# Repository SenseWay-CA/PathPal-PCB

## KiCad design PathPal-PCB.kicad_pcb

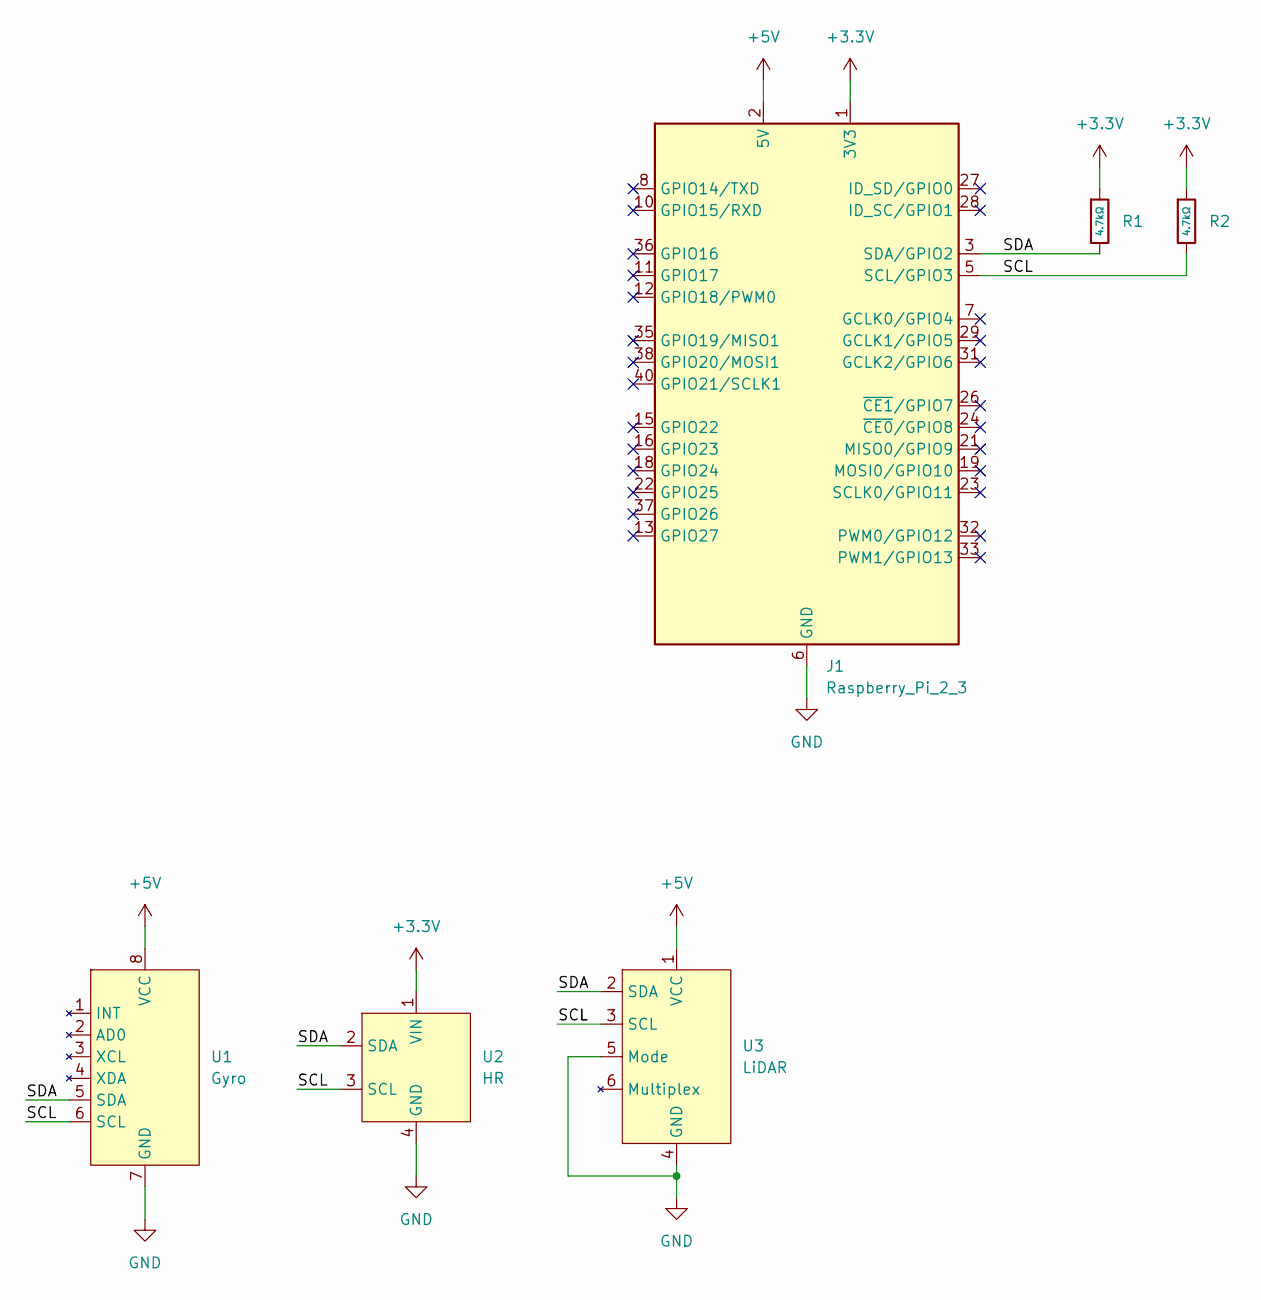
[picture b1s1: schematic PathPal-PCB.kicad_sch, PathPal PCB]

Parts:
J1: Raspberry_Pi_2_3; PinSocket_2x20_P2.54mm_Vertical
R1, R2: 4.7kΩ; R_Axial_DIN0207_L6.3mm_D2.5mm_P7.62mm_Horizontal; Overload Voltage (Max) 150V; Tolerance ±1%; Part 0805W8F4701T5E; LCSC C17673
U1: Gyro; PinSocket_1x08_P2.54mm_Vertical
U2: HR; PinSocket_1x04_P2.54mm_Vertical
U3: LiDAR; PinSocket_1x06_P2.54mm_Vertical

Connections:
+3.3V: J1.1 (3V3), J1.17 (3V3), R1.1, R2.1, U2.1 (VIN)
+5V: J1.2 (5V), J1.4 (5V), U1.8 (VCC), U3.1 (VCC)
/SCL: J1.5 (SCL/GPIO3), R2.2, U1.6 (SCL), U2.3 (SCL), U3.3 (SCL)
/SDA: J1.3 (SDA/GPIO2), R1.2, U1.5 (SDA), U2.2 (SDA), U3.2 (SDA)
GND: J1.6 (GND), J1.9 (GND), J1.14 (GND), J1.20 (GND), J1.25 (GND), J1.30 (GND), J1.34 (GND), J1.39 (GND), U1.7 (GND), U2.4 (GND), U3.4 (GND), U3.5 (Mode)

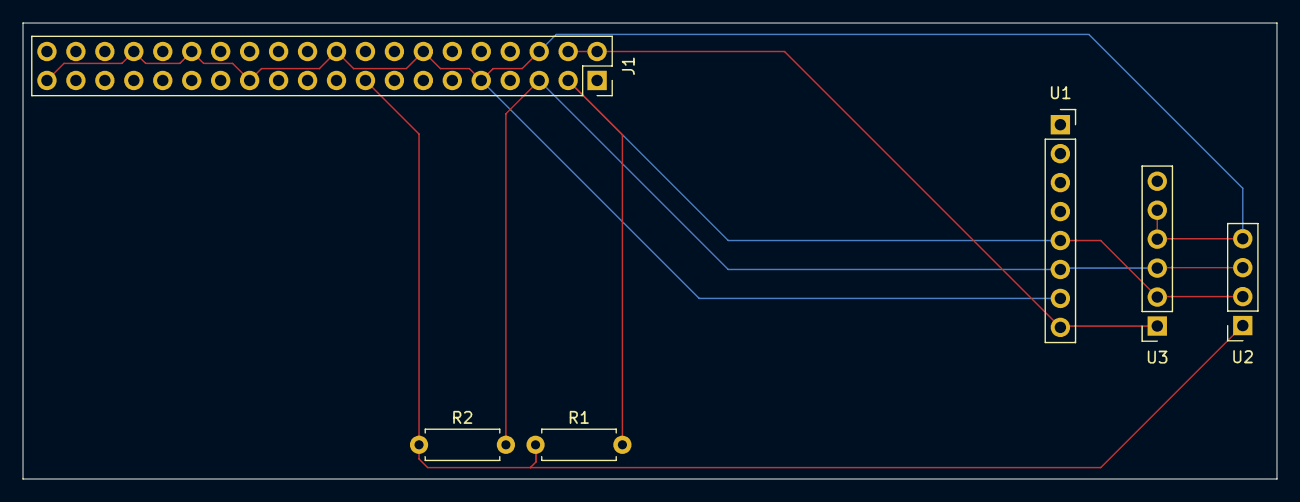
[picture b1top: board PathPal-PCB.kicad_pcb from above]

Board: 4 copper layers, 110.0 x 40.0 mm, 6 parts (0 on the bottom side), 5 nets.

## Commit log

2026-02-18 schematic done
2026-02-19 parts layout done
2026-02-24 moved parts
2026-03-25 Fixed Routing
2026-03-25 Added Labels Silkscreen
2026-03-25 Added Logo
2026-03-25 Order
2026-03-31 simpler
2026-03-31 removed old production files
